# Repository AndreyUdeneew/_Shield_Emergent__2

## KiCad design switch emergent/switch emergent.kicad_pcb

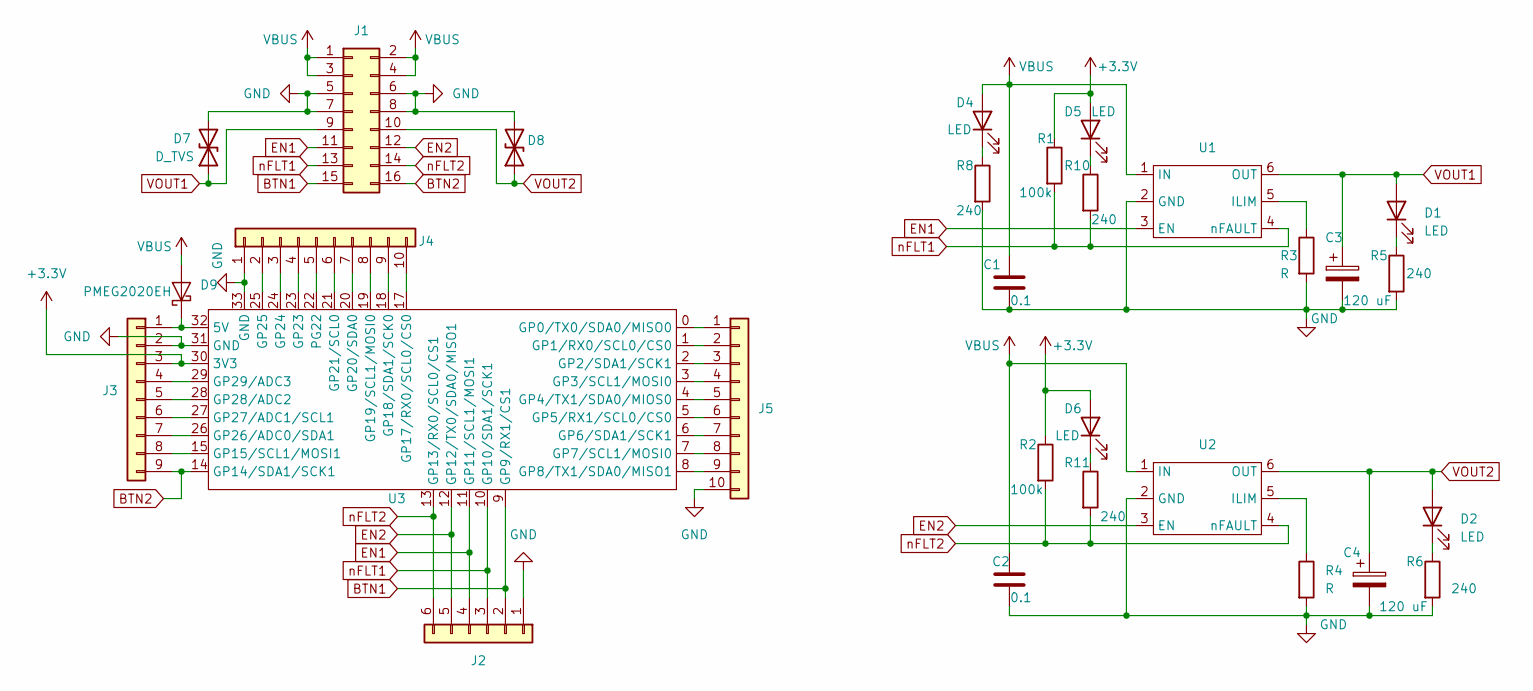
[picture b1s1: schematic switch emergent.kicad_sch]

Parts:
C1, C2: 0.1; C_0603_1608Metric_Pad1.08x0.95mm_HandSolder
C3, C4: 120 uF; CP_Elec_6.3x7.7
D1, D2, D4, D5, D6: LED; LED_0603_1608Metric_Pad1.05x0.95mm_HandSolder
D7, D8: D_TVS; D_SOD-123F
D9: PMEG2020EH; D_SOD-123F
J1: Conn_02x08_Odd_Even; PinSocket_2x08_P2.54mm_Vertical
J2: Conn_01x06; PinHeader_1x06_P2.54mm_Vertical
J3: Conn_01x09; PinHeader_1x09_P2.54mm_Vertical
J4, J5: Conn_01x10; PinSocket_1x10_P2.54mm_Vertical
R1, R2: 100k; R_0603_1608Metric_Pad0.98x0.95mm_HandSolder
R3, R4: R; R_0603_1608Metric_Pad0.98x0.95mm_HandSolder
R5, R6, R8, R10, R11: 240; R_0603_1608Metric_Pad0.98x0.95mm_HandSolder
U1, U2: SOT-23-6_Handsoldering
U3: RP2040Zero

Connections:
+3.3V: D5.2 (A), D6.2 (A), J3.3, R1.1, R2.1, U3.30 (3V3)
BTN1: J1.15, J2.2, U3.9 (GP9/RX1/CS1)
BTN2: J1.16, J3.9, U3.14 (GP14/SDA1/SCK1)
EN1: J1.11, J2.4, U1.3 (EN), U3.11 (GP11/SCL1/MOSI1)
EN2: J1.12, J2.5, U2.3 (EN), U3.12 (GP12/TX0/SDA0/MISO1)
GND: C1.2, C2.2, C3.2, C4.2, D7.2 (A2), D8.2 (A2), J1.5, J1.6, J1.7, J1.8, J2.1, J3.2, J4.1, J5.10, R3.2, R4.2, R5.2, R6.2, R8.2, U1.2 (GND), U2.2 (GND), U3.31 (GND), U3.33 (GND)
unnamed: D1.1 (K), R5.1
unnamed: D2.1 (K), R6.1
unnamed: D4.1 (K), R8.1
unnamed: D5.1 (K), R10.1
unnamed: D6.1 (K), R11.1
unnamed: D9.1 (K), J3.1, U3.32 (5V)
unnamed: J3.4, U3.29 (GP29/ADC3)
unnamed: J3.5, U3.28 (GP28/ADC2)
unnamed: J3.6, U3.27 (GP27/ADC1/SCL1)
unnamed: J3.7, U3.26 (GP26/ADC0/SDA1)
unnamed: J3.8, U3.15 (GP15/SCL1/MOSI1)
unnamed: J4.2, U3.25 (GP25)
unnamed: J4.3, U3.24 (GP24)
unnamed: J4.4, U3.23 (GP23)
unnamed: J4.5, U3.22 (PG22)
unnamed: J4.6, U3.21 (GP21/SCL0)
unnamed: J4.7, U3.20 (GP20/SDA0)
unnamed: J4.8, U3.19 (GP19/SCL1/MOSI0)
unnamed: J4.9, U3.18 (GP18/SDA1/SCK0)
unnamed: J4.10, U3.17 (GP17/RX0/SCL0/CS0)
unnamed: J5.1, U3.0 (GP0/TX0/SDA0/MISO0)
unnamed: J5.2, U3.1 (GP1/RX0/SCL0/CS0)
unnamed: J5.3, U3.2 (GP2/SDA1/SCK1)
unnamed: J5.4, U3.3 (GP3/SCL1/MOSI0)
unnamed: J5.5, U3.4 (GP4/TX1/SDA0/MIOS0)
unnamed: J5.6, U3.5 (GP5/RX1/SCL0/CS0)
unnamed: J5.7, U3.6 (GP6/SDA1/SCK1)
unnamed: J5.8, U3.7 (GP7/SCL1/MOSI0)
unnamed: J5.9, U3.8 (GP8/TX1/SDA0/MISO1)
unnamed: R3.1, U1.5 (ILIM)
unnamed: R4.1, U2.5 (ILIM)
VBUS: C1.1, C2.1, D4.2 (A), D9.2 (A), J1.1, J1.2, J1.3, J1.4, U1.1 (IN), U2.1 (IN)
VOUT1: C3.1, D1.2 (A), D7.1 (A1), J1.9, U1.6 (OUT)
VOUT2: C4.1, D2.2 (A), D8.1 (A1), J1.10, U2.6 (OUT)
nFLT1: J1.13, J2.3, R1.2, R10.2, U1.4 (nFAULT), U3.10 (GP10/SDA1/SCK1)
nFLT2: J1.14, J2.6, R2.2, R11.2, U2.4 (nFAULT), U3.13 (GP13/RX0/SCL0/CS1)

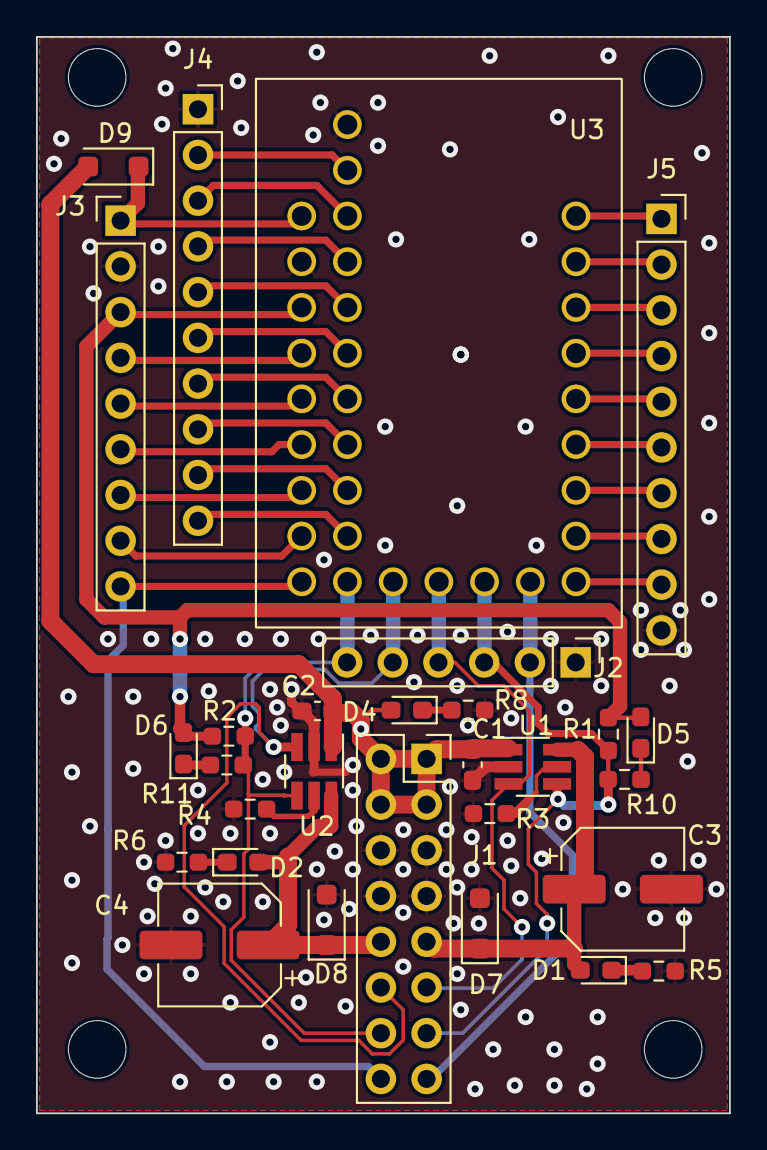
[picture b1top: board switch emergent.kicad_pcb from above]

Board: 2 copper layers, 38.5 x 59.8 mm, 29 parts (0 on the bottom side), 42 nets.

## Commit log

2024-05-08 v0.1 Seems 2B ready
2024-05-12 v0.2 Ordered
2024-06-05 v0.3 universal PCB for embedded and remote swithces
2024-06-06 v0.4 PCB uluchshaizing
2024-06-06 v0.5 ordered advanced with embedded and remote switches
